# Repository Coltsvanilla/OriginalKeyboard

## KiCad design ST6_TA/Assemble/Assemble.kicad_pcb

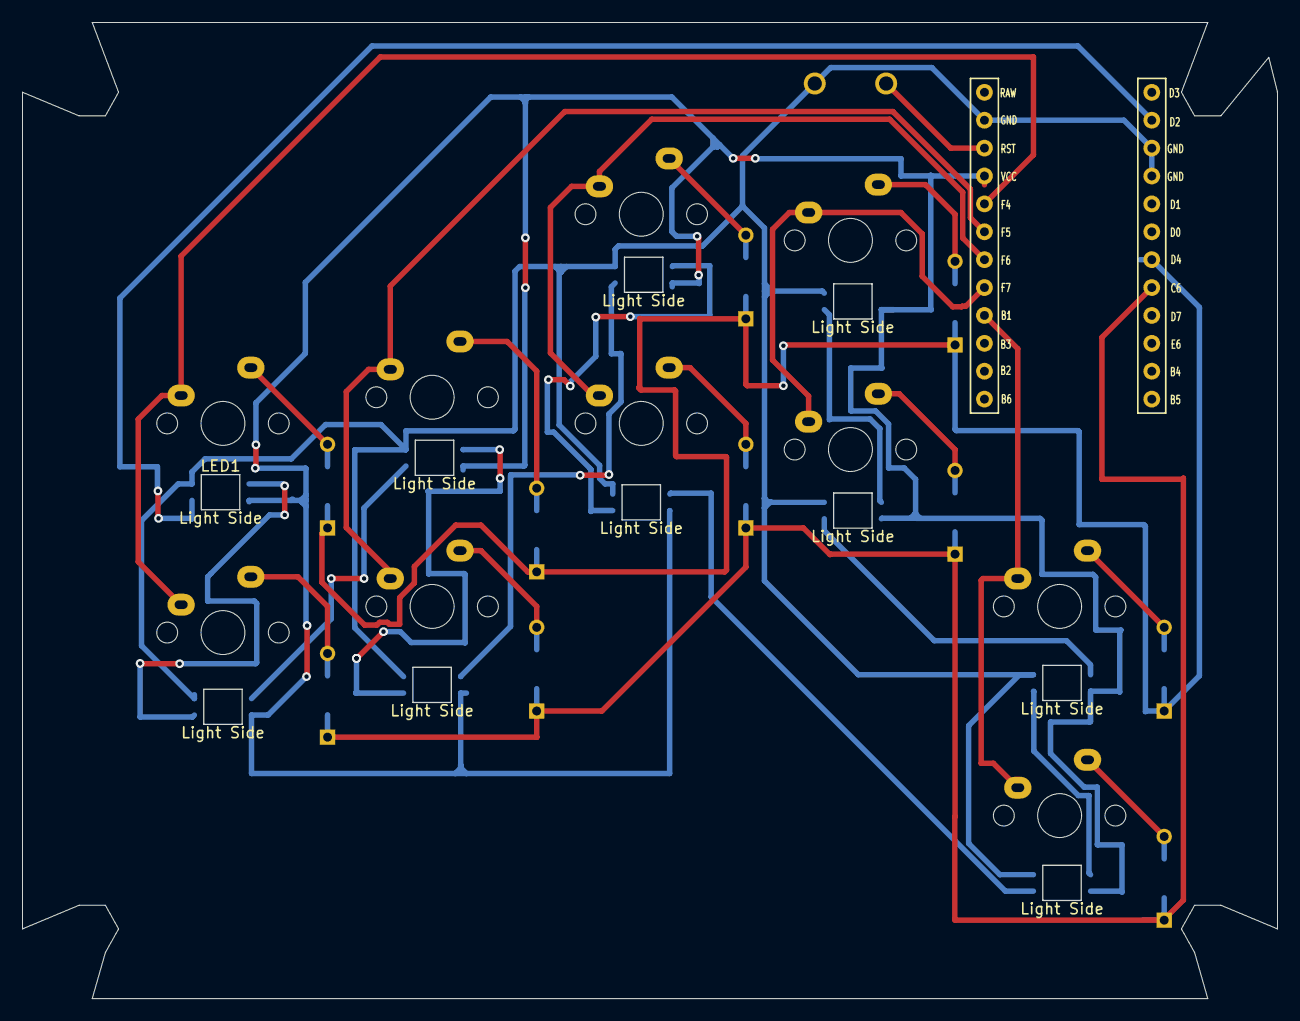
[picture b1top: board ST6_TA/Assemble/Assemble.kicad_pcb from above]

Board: 2 copper layers, 114.3 x 88.9 mm, 32 parts (1 on the bottom side), 30 nets.

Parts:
D1, D2, D3, D4, D5, D6, D7, D8, D9, D10: D; Diode_TH_SMD
LED1, LED2, LED3, LED4, LED5, LED6, LED7, LED8, LED9, LED10: LED_SK6812MINI-E; LED_SK6812MINI-E_BL
SW1, SW2, SW3, SW4, SW5, SW6, SW7, SW8, SW9, SW10: SW_PUSH; CherryMX_Solder_1u
SW11: SW_PUSH; ResetSW
U1: ProMicro; Micon_ProMicro

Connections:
Col0: SW1.1, SW2.1, U1.20 (F4/A3)
Col1: SW3.1, SW4.1, U1.19 (F5/A2)
Col2: SW5.1, SW6.1, U1.18 (F6/A1)
Col3: SW7.1, SW8.1, U1.17 (F7/A0)
Col4: SW9.1, SW10.1, U1.16 (B1/15)
GND: LED1.2 (VSS), LED2.2 (VSS), LED3.2 (VSS), LED4.2 (VSS), LED5.2 (VSS), LED6.2 (VSS), LED7.2 (VSS), LED8.2 (VSS), LED9.2 (VSS), LED10.2 (VSS), SW11.2, U1.3 (GND), U1.4 (GND), U1.23 (GND)
LED: LED1.3 (DIN), U1.2 (RX1/D2)
Low0: D1.1 (K), D3.1 (K), D5.1 (K), D7.1 (K), D9.1 (K), U1.7 (4/D4)
Low1: D2.1 (K), D4.1 (K), D6.1 (K), D8.1 (K), D10.1 (K), U1.8 (5/C6)
unnamed: D1.2 (A), SW1.2
unnamed: D2.2 (A), SW2.2
unnamed: D3.2 (A), SW3.2
unnamed: D4.2 (A), SW4.2
unnamed: D5.2 (A), SW5.2
unnamed: D6.2 (A), SW6.2
unnamed: D7.2 (A), SW7.2
unnamed: D8.2 (A), SW8.2
unnamed: D9.2 (A), SW9.2
unnamed: D10.2 (A), SW10.2
unnamed: LED1.1 (DOUT), LED2.3 (DIN)
unnamed: LED2.1 (DOUT), LED3.3 (DIN)
unnamed: LED3.1 (DOUT), LED4.3 (DIN)
unnamed: LED4.1 (DOUT), LED5.3 (DIN)
unnamed: LED5.1 (DOUT), LED6.3 (DIN)
unnamed: LED6.1 (DOUT), LED7.3 (DIN)
unnamed: LED7.1 (DOUT), LED8.3 (DIN)
unnamed: LED8.1 (DOUT), LED9.3 (DIN)
unnamed: LED9.1 (DOUT), LED10.3 (DIN)
Rest: SW11.1, U1.22 (RST)
VCC: LED1.4 (VDD), LED2.4 (VDD), LED3.4 (VDD), LED4.4 (VDD), LED5.4 (VDD), LED6.4 (VDD), LED7.4 (VDD), LED8.4 (VDD), LED9.4 (VDD), LED10.4 (VDD), U1.21 (VCC)

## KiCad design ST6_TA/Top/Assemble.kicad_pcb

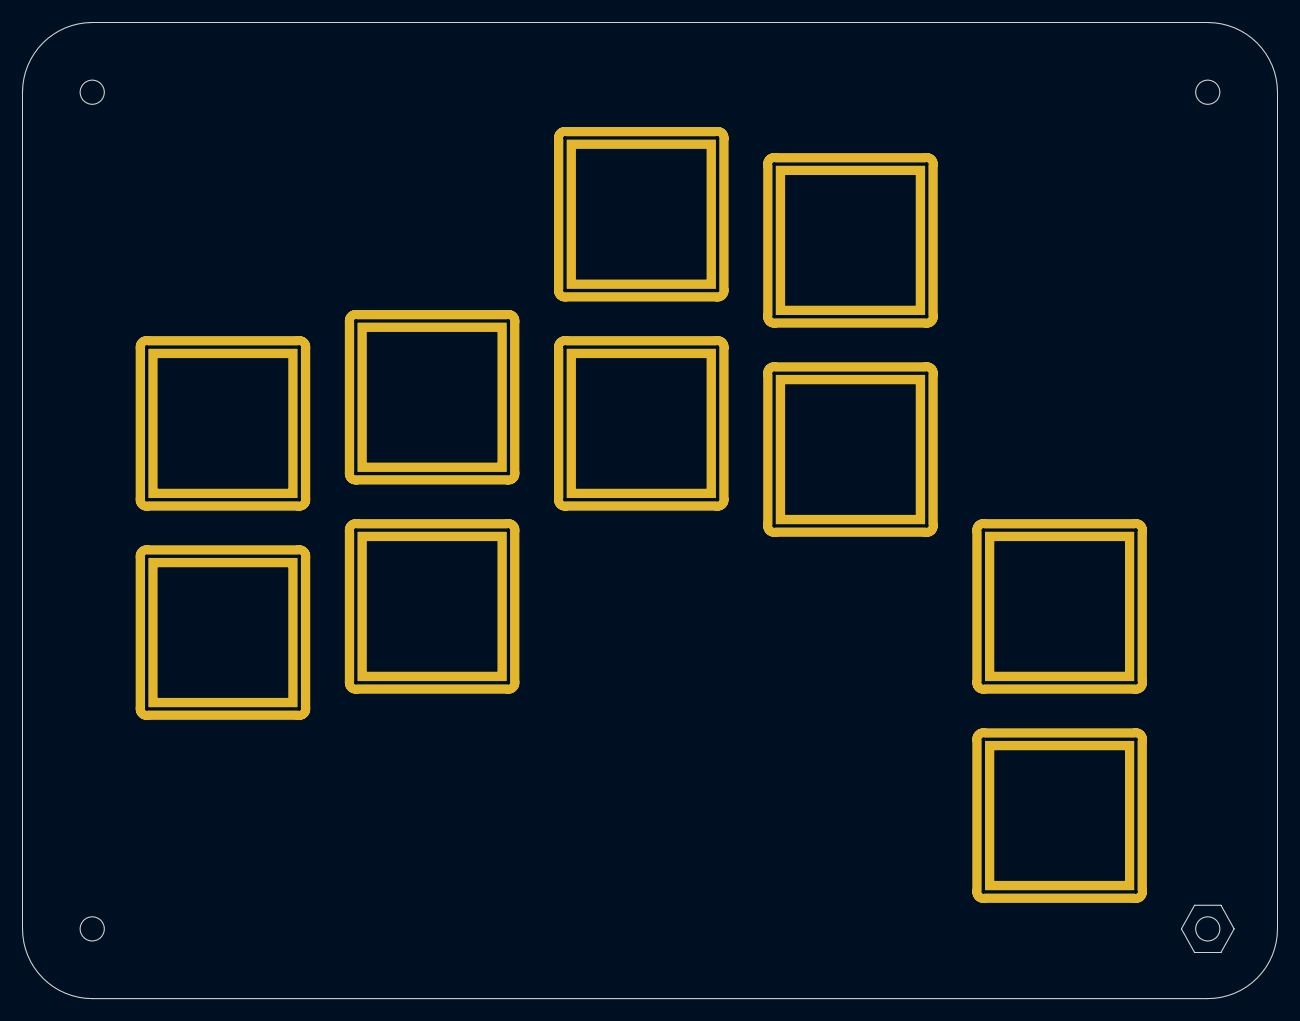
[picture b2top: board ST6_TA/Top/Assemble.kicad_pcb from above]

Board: 2 copper layers, 114.3 x 88.9 mm, 15 parts (0 on the bottom side), 5 nets, no tracks yet.

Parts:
Ref**: Val**; m2_Spacer_Hole_hex
Ref**#2, Ref**#3, Ref**#4, Ref**#5: Val**; m2_Screw_Hole
SW1, SW2, SW3, SW4, SW5, SW6, SW7, SW8, SW9, SW10: SW_PUSH; SW_Hole_TH_1u

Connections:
Col0: SW1.1, SW2.1
Col1: SW3.1, SW4.1
Col2: SW5.1, SW6.1
Col3: SW7.1, SW8.1
Col4: SW9.1, SW10.1

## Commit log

2023-11-16 キーボードのレイアウト作成
2023-11-16 ST6用キーボードレイアウトの作成
2023-11-16 キーボード基盤、キーレイヤーの追加
2023-11-16 基盤配線前
2023-11-16 ネジ穴検討
2023-11-17 Top,Bottom,Assenbleのネジ穴確定
2023-11-17 配線完了
2023-11-17 ファイル名変更前
2023-11-20 ソケット部分を通常のものに変更
